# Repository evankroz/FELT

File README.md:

# FELT - Flight Environment Logging and Telemetry
A *light*weight (light as felt) Arduino system for logging, primarily altitude, data using the Adafruit Feather M0 Adalogger and DPS310 pressure sensor.

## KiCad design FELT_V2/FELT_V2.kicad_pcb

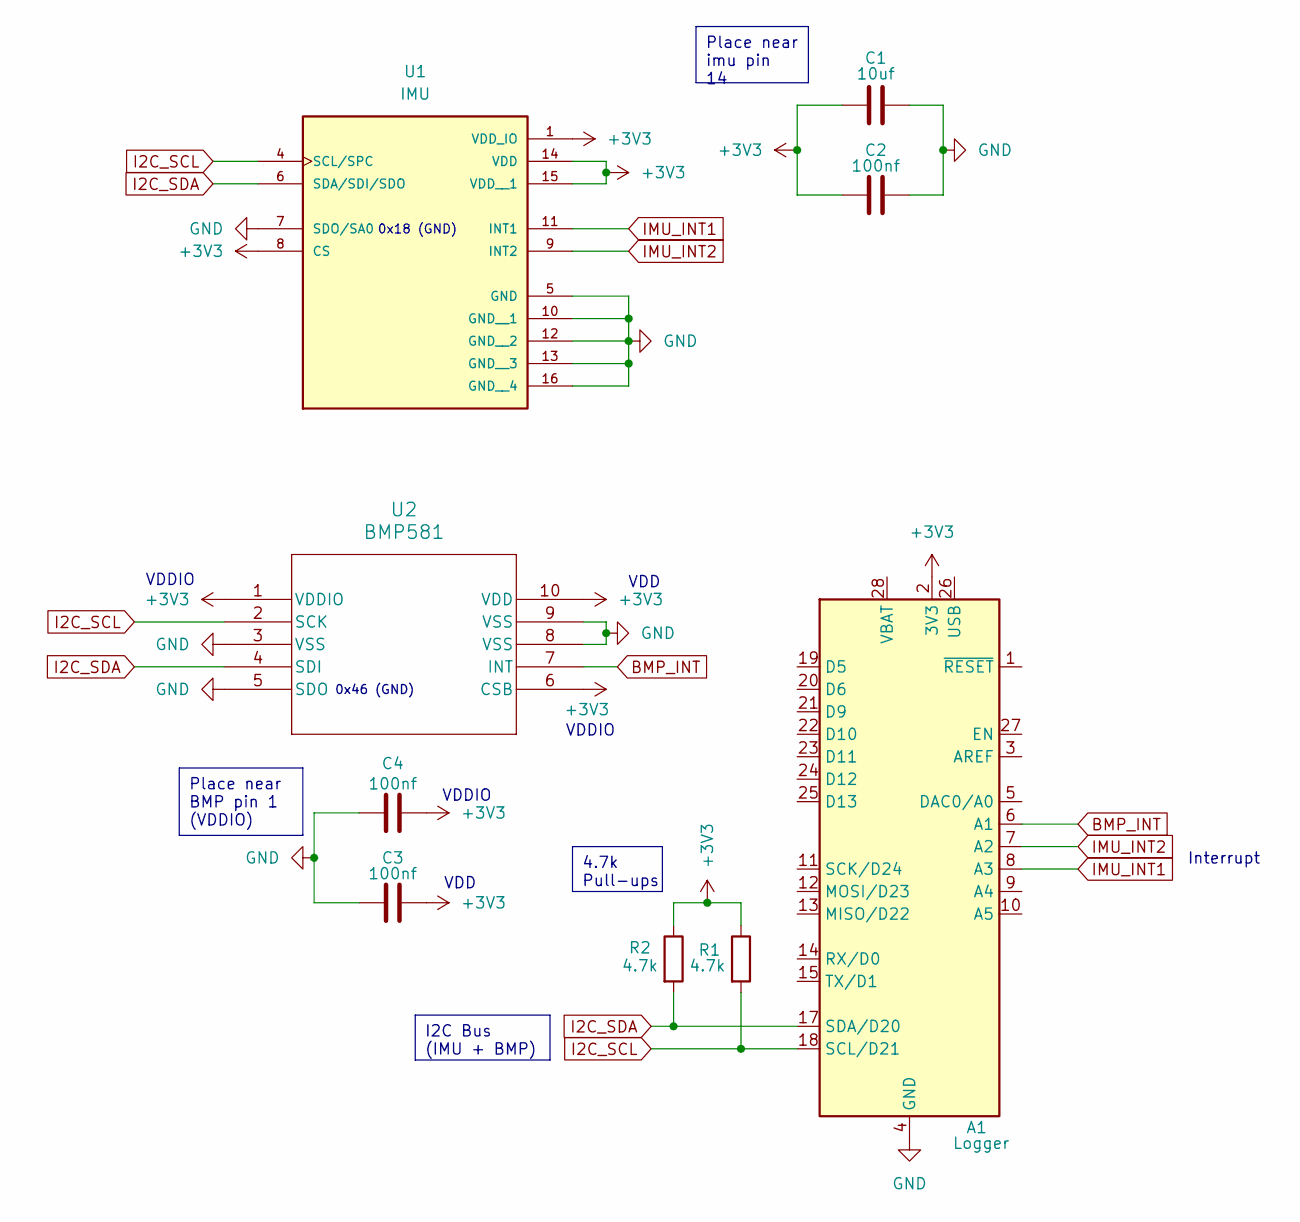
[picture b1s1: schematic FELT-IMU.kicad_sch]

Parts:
A1: Logger; Adafruit_Feather
C1: 10uf; CAPC1608X90N
C2, C3, C4: 100nf; CAPC1608X90N
R1, R2: 4.7k; STA_CF14_STP
U1: IMU; QFN300X300X100-16N
U2: BMP581; QFN10_BMP581_BOS

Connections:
+3V3: A1.2 (3V3), C1.1, C2.1, C3.2, C4.2, R1.1, R2.1, U1.1 (VDD_IO), U1.8 (CS), U1.14 (VDD), U1.15 (VDD__1), U2.1 (VDDIO), U2.6 (CSB), U2.10 (VDD)
BMP_INT: A1.6 (A1), U2.7 (INT)
GND: A1.4 (GND), A1.16 (GND), C1.2, C2.2, C3.1, C4.1, U1.5 (GND), U1.7 (SDO/SA0), U1.10 (GND__1), U1.12 (GND__2), U1.13 (GND__3), U1.16 (GND__4), U2.3 (VSS), U2.5 (SDO), U2.8 (VSS), U2.9 (VSS)
I2C_SCL: A1.18 (SCL/D21), R1.2, U1.4 (SCL/SPC), U2.2 (SCK)
I2C_SDA: A1.17 (SDA/D20), R2.2, U1.6 (SDA/SDI/SDO), U2.4 (SDI)
IMU_INT1: A1.8 (A3), U1.11 (INT1)
IMU_INT2: A1.7 (A2), U1.9 (INT2)

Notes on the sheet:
I2C Bus (IMU + BMP)
4.7k Pull-ups
Place near imu pin 14
Place near BMP pin 1 (VDDIO)
VDD
VDDIO
0x46 (GND)
0x18 (GND)
Interrupt

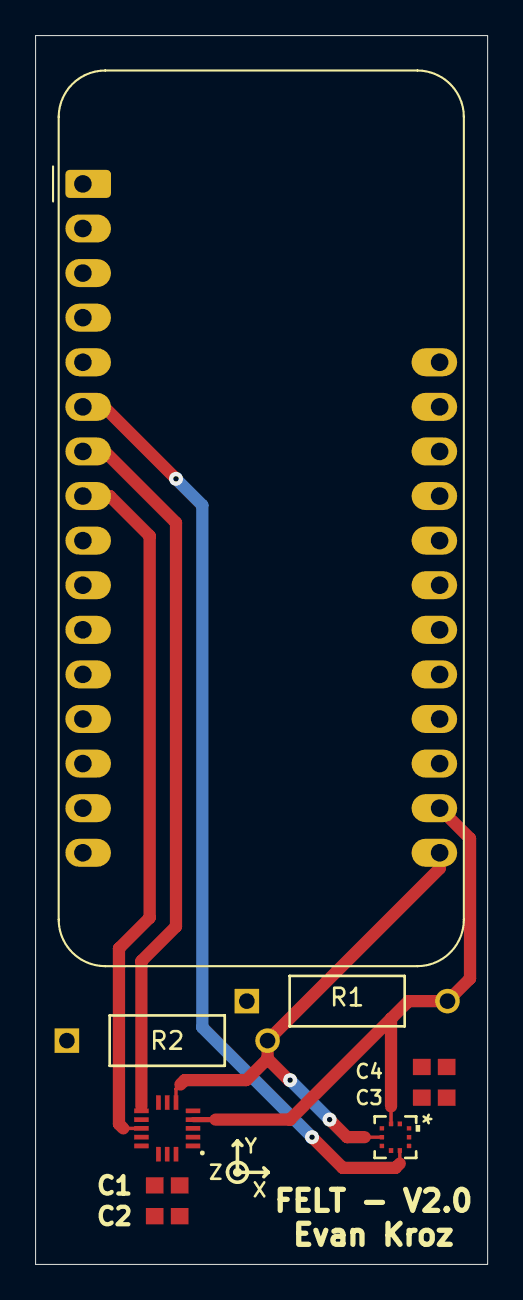
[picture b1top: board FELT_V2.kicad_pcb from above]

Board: 4 copper layers, 25.8 x 70.0 mm, 9 parts (0 on the bottom side), 7 nets.

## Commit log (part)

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2026-01-01 Rename project from Alti-Logger to FELT
2026-01-02 Rename altilogbott-edited.jpg to felt.jpg
2026-01-02 Add image link to README for FELT system
2026-01-02 Correct image link in README
    Fix image link formatting in README.md
2026-01-02 Rename ADALOGGER.ino to feltmain.ino
